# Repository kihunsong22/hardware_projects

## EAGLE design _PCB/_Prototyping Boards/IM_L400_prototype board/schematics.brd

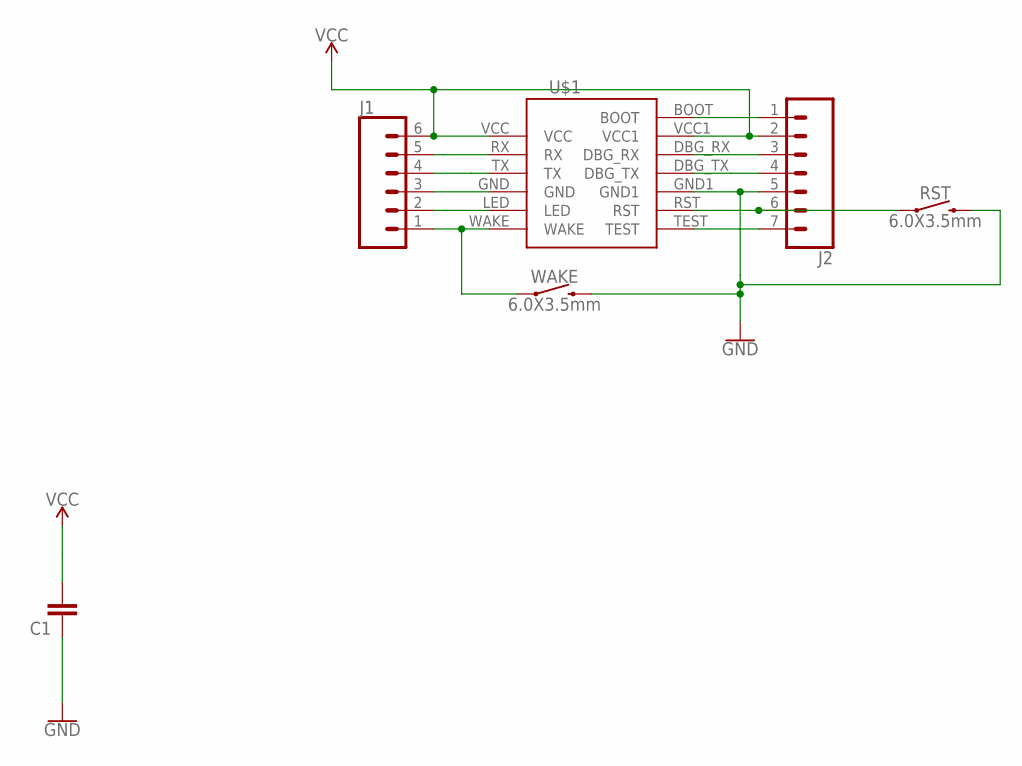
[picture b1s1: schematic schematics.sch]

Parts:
C1: C-EUC0805; C0805
J1: CONN_06LOCK; 1X06_LOCK
J2: CONN_07LOCK; 1X07_LOCK
RST: 6.0X3.5mm; TACTILE_SWITCH_SMD_6.0X3.5MM
U$1: IM-L400
WAKE: 6.0X3.5mm; TACTILE_SWITCH_SMD_6.0X3.5MM

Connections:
GND: C1.1, J1.3, J2.5, RST.2, U$1.GND, U$1.GND1, WAKE.2
unnamed: J1.5, U$1.RX
unnamed: J1.4, U$1.TX
unnamed: J1.2, U$1.LED
unnamed: J1.1, U$1.WAKE, WAKE.1
unnamed: J2.1, U$1.BOOT
unnamed: J2.3, U$1.DBG_RX
unnamed: J2.4, U$1.DBG_TX
unnamed: J2.6, RST.1, U$1.RST
unnamed: J2.7, U$1.TEST
VCC: C1.2, J1.6, J2.2, U$1.VCC, U$1.VCC1

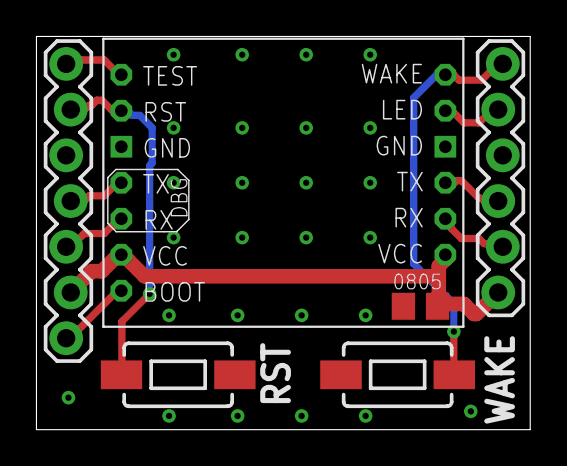
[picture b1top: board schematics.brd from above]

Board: 2 copper layers, 27.4 x 21.8 mm, 6 parts (0 on the bottom side), 11 nets.

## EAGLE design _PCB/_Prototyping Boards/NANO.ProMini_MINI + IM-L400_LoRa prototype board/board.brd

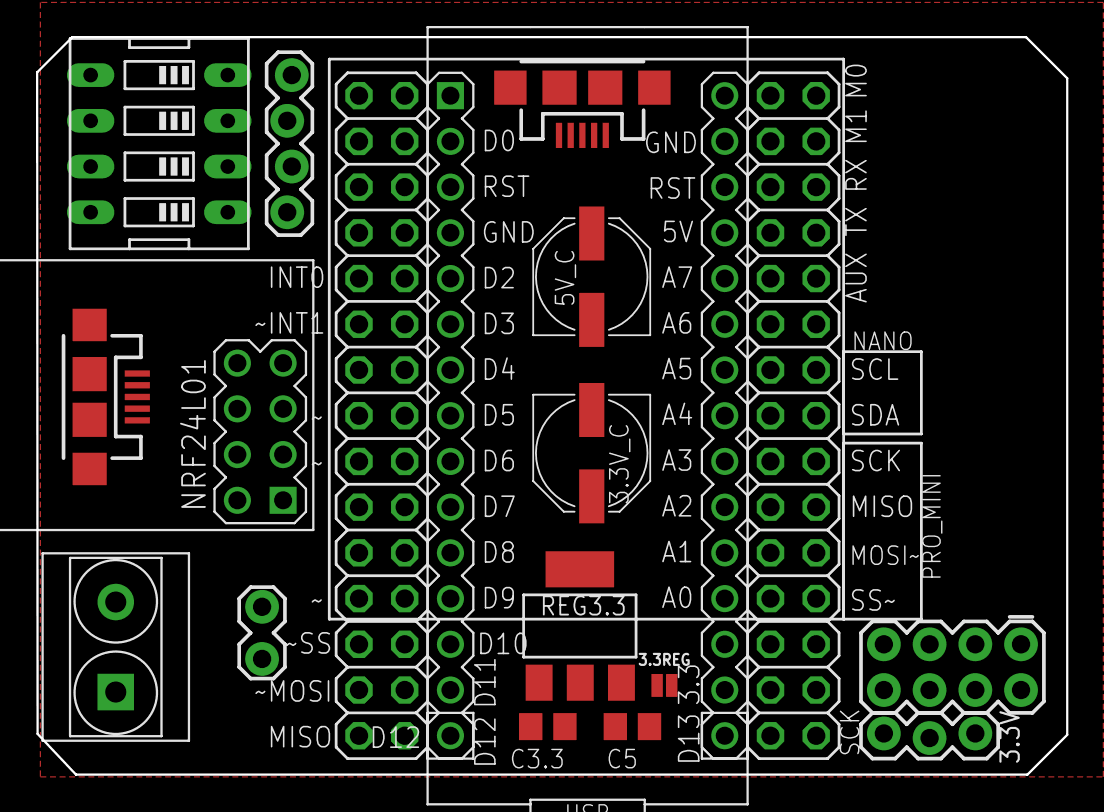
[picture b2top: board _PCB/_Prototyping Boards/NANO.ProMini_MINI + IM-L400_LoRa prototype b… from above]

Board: 2 copper layers, 57.2 x 41.0 mm, 18 parts (0 on the bottom side), 38 nets, no tracks yet.

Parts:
3.3REG: SMT-JUMPER_2_NO_NO-SILK
3.3V: 1X03_LOCK
3.3V_C, 5V_C: PANASONIC_D
5.GND: 2X4
C3.3, C5: 100nF; C0805
J4: 1X04_LOCK
MICRO_1, MICRO_2: USB-MICROB
NANO: ARDUINO-NANO-3.0
NRF24L01: WIRELESS-NRF24L01
PH1, PH2: 2X15
PIN1: 1X02_LOCK
REG3.3: REG1117; SOT223
SW1: EDG-04
T1_5MM: 5mm; H2-5.0-10.5X8.0MM

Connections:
3.3V: 3.3V.1, 3.3V.2, 3.3V.3, 3.3V_C.+, NANO.J2.14, NRF24L01.2, PH1.3, PH1.4
5V: 5.GND.2, 5.GND.4, 5.GND.6, 5.GND.8, 5V_C.+, C5.1, MICRO_1.VBUS, MICRO_2.VBUS, NANO.J2.4, PH1.23, PH1.24, REG3.3.3
A5: NANO.J2.7, PH1.17, PH1.18
A6: NANO.J2.6, PH1.19, PH1.20
A7: NANO.J2.5, PH1.21, PH1.22
CE_NRF: NANO.J1.9, NRF24L01.3, PH2.13, PH2.14
CSN_NRF: NANO.J1.8, NRF24L01.4, PH2.15, PH2.16
GND: 3.3V_C.-, 5.GND.1, 5.GND.3, 5.GND.5, 5.GND.7, 5V_C.-, C3.3.1, C5.2, MICRO_1.GND, MICRO_2.GND, NANO.J2.2, NRF24L01.1, PH1.27, PH1.28, REG3.3.1, SW1.5, SW1.6, SW1.7, SW1.8
MISO_NRF: NANO.J1.4, NRF24L01.7, PH2.23, PH2.24
MOSI_NRF: NANO.J1.5, NRF24L01.6, PH2.21, PH2.22
unnamed: 3.3REG.2, C3.3.2
unnamed: 3.3REG.1, REG3.3.2
unnamed: NANO.J2.13, PH1.5, PH1.6
unnamed: NANO.J2.12, PH1.7, PH1.8
unnamed: NANO.J2.11, PH1.9, PH1.10
unnamed: NANO.J2.10, PH1.11, PH1.12
unnamed: NANO.J2.9, PH1.13, PH1.14
unnamed: NANO.J2.8, PH1.15, PH1.16
unnamed: NANO.J1.15, PH2.1, PH2.2
unnamed: NANO.J1.14, PH2.3, PH2.4
unnamed: NANO.J1.13, PH2.5, PH2.6
unnamed: NANO.J1.12, PH2.7, PH2.8
unnamed: NANO.J1.11, PH2.9, PH2.10
unnamed: NANO.J1.10, PH2.11, PH2.12
unnamed: PIN1.2, T1_5MM.1
unnamed: NANO.J1.7, PH2.17, PH2.18
unnamed: NANO.J1.6, PH2.19, PH2.20
unnamed: PIN1.1, T1_5MM.2
unnamed: NANO.J1.3, PH2.25, PH2.26
unnamed: NANO.J1.2, PH2.27, PH2.28
unnamed: NANO.J1.1, PH2.29, PH2.30
unnamed: J4.1, SW1.4
unnamed: J4.2, SW1.3
unnamed: J4.3, SW1.2
unnamed: J4.4, SW1.1
RST: NANO.J2.3, PH1.25, PH1.26
SCK_NRF: NANO.J2.15, NRF24L01.5, PH1.1, PH1.2
VIN: NANO.J2.1, PH1.29, PH1.30

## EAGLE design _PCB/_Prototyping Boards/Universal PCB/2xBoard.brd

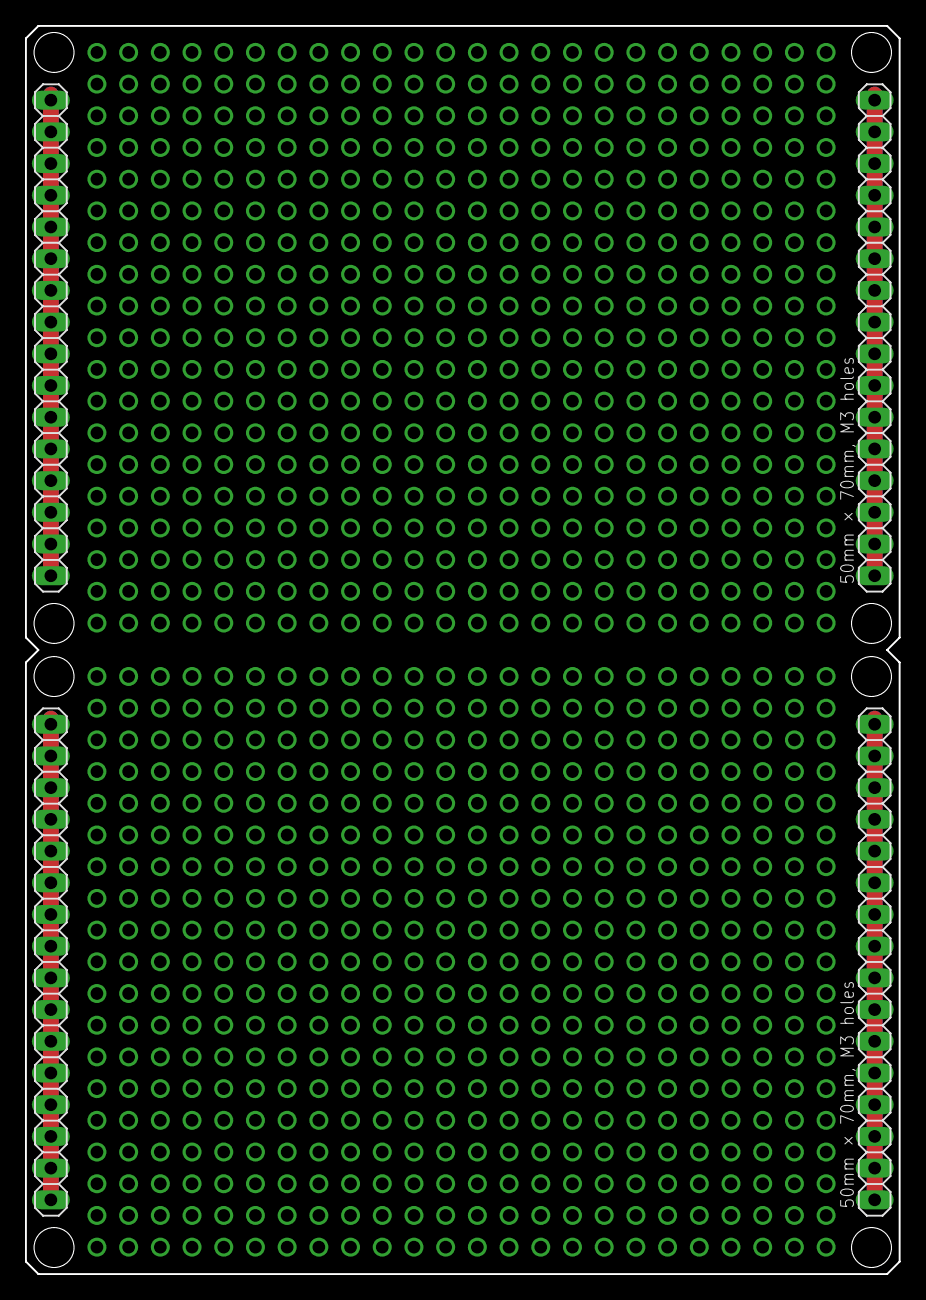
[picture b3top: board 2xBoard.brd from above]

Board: 2 copper layers, 70.0 x 100.0 mm, 4 parts (0 on the bottom side), 4 nets.

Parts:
JP1, JP2, JP3, JP4: 1X16

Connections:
SIDE1: JP4.1, JP4.2, JP4.3, JP4.4, JP4.5, JP4.6, JP4.7, JP4.8, JP4.9, JP4.10, JP4.11, JP4.12, JP4.13, JP4.14, JP4.15, JP4.16
SIDE2: JP3.1, JP3.2, JP3.3, JP3.4, JP3.5, JP3.6, JP3.7, JP3.8, JP3.9, JP3.10, JP3.11, JP3.12, JP3.13, JP3.14, JP3.15, JP3.16
SIDE3: JP2.1, JP2.2, JP2.3, JP2.4, JP2.5, JP2.6, JP2.7, JP2.8, JP2.9, JP2.10, JP2.11, JP2.12, JP2.13, JP2.14, JP2.15, JP2.16
SIDE4: JP1.1, JP1.2, JP1.3, JP1.4, JP1.5, JP1.6, JP1.7, JP1.8, JP1.9, JP1.10, JP1.11, JP1.12, JP1.13, JP1.14, JP1.15, JP1.16

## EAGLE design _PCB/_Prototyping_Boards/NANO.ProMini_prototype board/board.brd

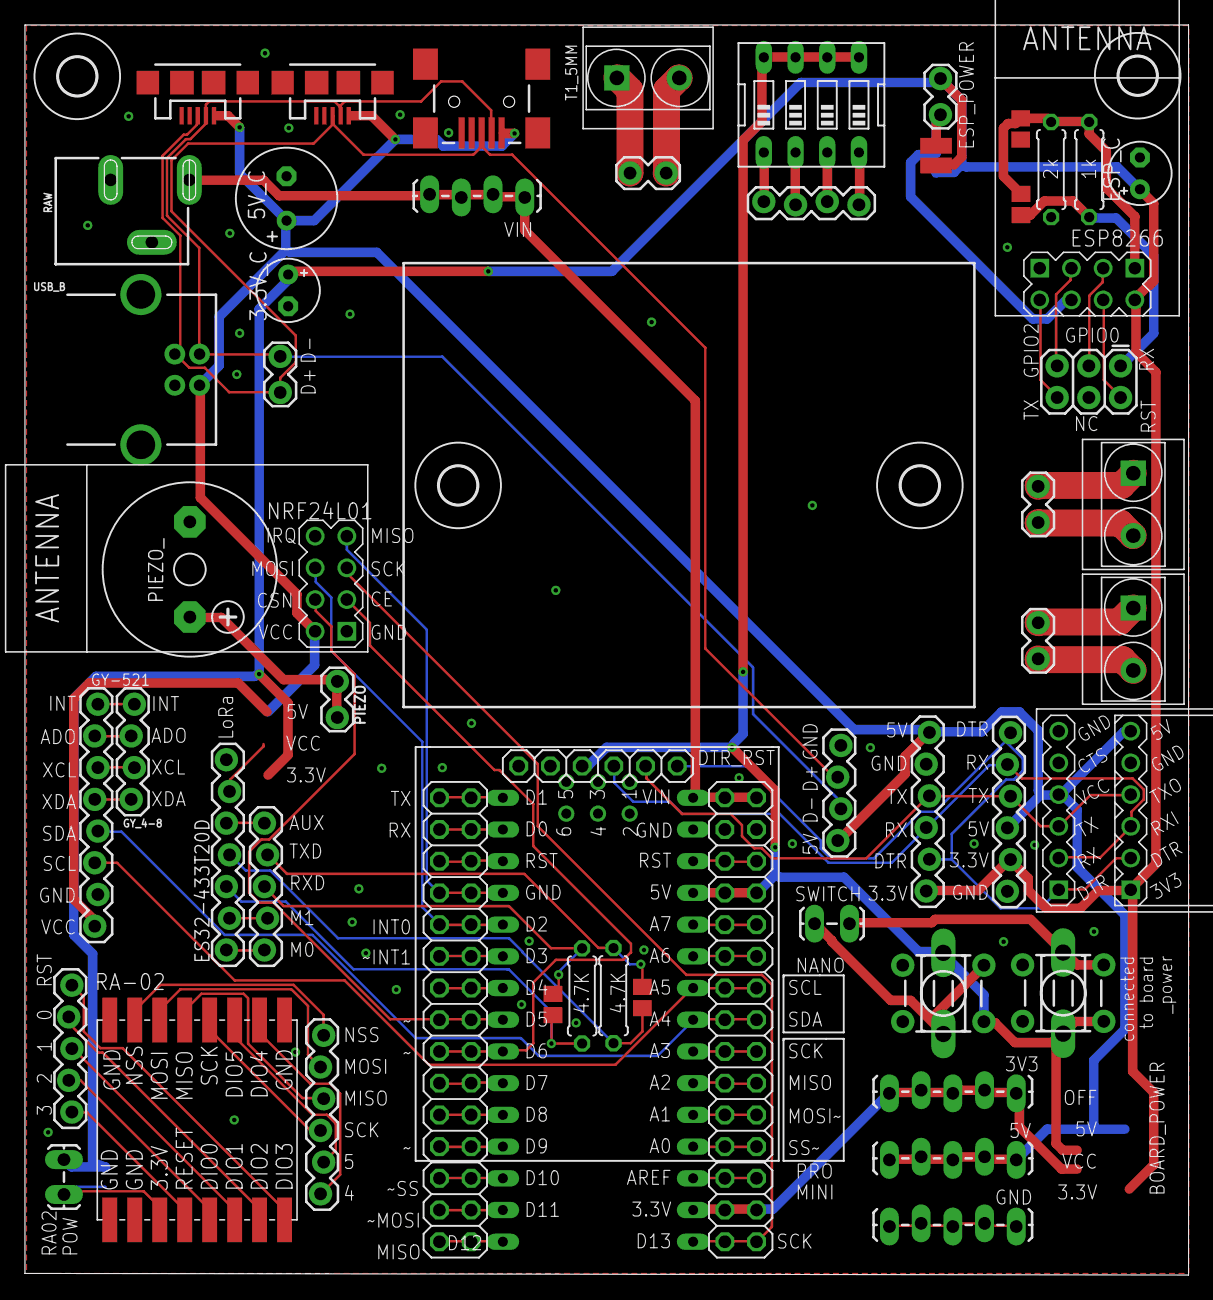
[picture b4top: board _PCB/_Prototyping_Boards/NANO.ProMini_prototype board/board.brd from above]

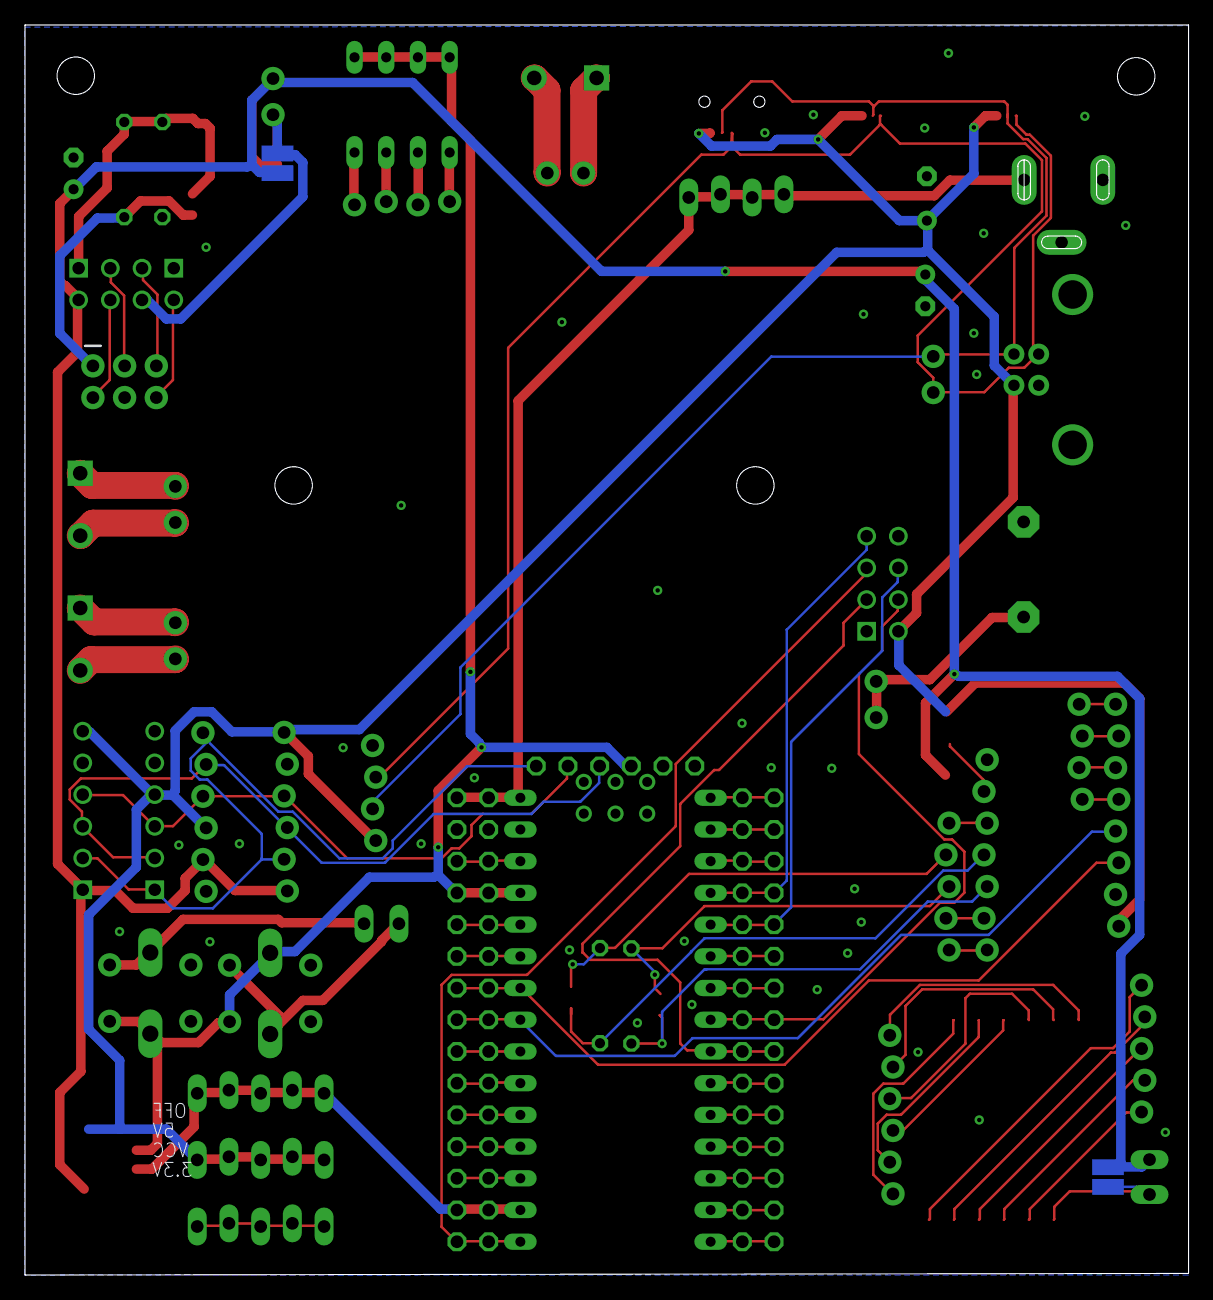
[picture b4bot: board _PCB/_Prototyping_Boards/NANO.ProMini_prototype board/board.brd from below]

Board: 2 copper layers, 93.2 x 100.1 mm, 68 parts (4 on the bottom side), 79 nets.

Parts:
3.3V, 5V: 1X05_LOCK_LONGPADS
3.3V_C: E2,5-5
5V_C: E3,5-8
B1: BREADBOARDMINI; BREADBOARD-MINI
CP2102_USB-SERIAL: USB-SERIAL-CP2102
ES32-433T20D: 1X07_LOCK
ESP1: 1k; 0207/7
ESP1_1, ESP2_1: R2012
ESP2: 2k; 0207/7
ESP8266: WIRELESS-WIFI-ESP-01
ESP_C: E2,5-5
ESP_H: 2X3
ESP_POW: 1X02_LOCK
GND: 1X05_LOCK_LONGPADS
GY-521: 1X08_LOCK
GY_4-8: 1X04_LOCK
H1, H2, H3, H4: MOUNT-HOLE3.0; 3,0
J1, J6: 1X05_LOCK
J2, J3: 1X02_LOCK_LONGPADS
J4, J8: 1X04_LOCK
J5, J7, J9: 1X06_LOCK
MICRO_1, MICRO_2: USB-MICROB
MINI_1: USB_MINI-B_SMT; USB-MINIB
NANO: NANO
NRF24L01: WIRELESS-NRF24L01
PAD1, PAD2, PAD3, PAD4, PAD5, PAD6: SMD1,27-2,54
PH1, PH2: 2X15
PIEZO: 1X02_LOCK
PIEZO_: F/CM12P
PIN1, PIN2, PIN3: 1X02_LOCK
PROMINI_H: 1X06/OCT
R1: 4.7k; 0207/7
R1_1, R2_1: R2012
R2: 4.7K; 0207/7
RA-02: LORA-RA2-SMD
RAW: POWER_JACK_SLOT
S1, S2: MOMENTARY-SWITCH-SPST-PTH-6.0MM; TACTILE_SWITCH_PTH_6.0MM
S3, S4: DTS-3
SW1: EDG-04
T1_5MM, T2_5MM, T3_5MM: 5mm; H2-5.0-10.5X8.0MM
U$1: USB-SERIAL-FT232R
USB_B: USB-B-PTH
USB_DATA: 1X02_LOCK
VIN: 1X04_LOCK_LONGPADS

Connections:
3.3V: 3.3V.1, 3.3V.2, 3.3V.3, 3.3V.4, 3.3V.5, 3.3V_C.+, CP2102_USB-SERIAL.1, ES32-433T20D.6, ESP8266.D2, ESP_C.+, ESP_POW.1, J3.1, J7.2, J9.1, NANO.3.3V, NRF24L01.2, PAD1.1, PAD3.1, PAD5.1, PH1.3, PH1.4
5V: 5V.1, 5V.2, 5V.3, 5V.4, 5V.5, 5V_C.+, CP2102_USB-SERIAL.6, GY-521.1, J7.3, J8.1, J9.6, MICRO_1.VBUS, MICRO_2.VBUS, MINI_1.VBUS, NANO.5V, PH1.23, PH1.24, PROMINI_H.3, U$1.4, USB_B.VBUS
A5: GY-521.3, NANO.A5, PH1.17, PH1.18
A6: NANO.A6, PH1.19, PH1.20
A7: NANO.A7, PH1.21, PH1.22
CE_NRF: NANO.D6, NRF24L01.3, PH2.13, PH2.14
CSN_NRF: NANO.D5, NRF24L01.4, PH2.15, PH2.16
D+_5PIN: J8.3, MICRO_1.D+, MICRO_2.D+, MINI_1.D+, USB_B.D+, USB_DATA.2
D-_5PIN: J8.2, MICRO_1.D-, MICRO_2.D-, MINI_1.D-, USB_B.D-, USB_DATA.1
GND: 3.3V_C.-, 5V_C.-, CP2102_USB-SERIAL.5, ES32-433T20D.7, ESP2.1, ESP2_1.1, ESP8266.A1, ESP_C.-, GY-521.2, J7.1, J8.4, J9.5, MICRO_1.GND, MICRO_2.GND, MINI_1.GND, NANO.GND, NANO.ICSP6, NRF24L01.1, PH1.27, PH1.28, PIEZO_.-, PROMINI_H.1, RA-02.1, RA-02.2, RA-02.9, RA-02.16, RAW.GND@1, S1.1, S2.1, S3.1, S4.2, SW1.5, SW1.6, SW1.7, SW1.8, U$1.6, USB_B.GND
MISO_NRF: NANO.GND1, NRF24L01.7, PH2.23, PH2.24
MOSI_NRF: NANO.D2, NRF24L01.6, PH2.21, PH2.22
unnamed: ES32-433T20D.2, J1.2
unnamed: GY-521.5, GY_4-8.4
unnamed: NANO.AREF, PH1.5, PH1.6
unnamed: NANO.A0, PH1.7, PH1.8
unnamed: NANO.A1, PH1.9, PH1.10
unnamed: NANO.A2, PH1.11, PH1.12
unnamed: NANO.A3, PH1.13, PH1.14
unnamed: GY-521.6, GY_4-8.3
unnamed: GY-521.7, GY_4-8.2
unnamed: GY-521.8, GY_4-8.1
unnamed: ES32-433T20D.1, J1.1
unnamed: J1.4, R1.1, R1_1.1
unnamed: J1.3, R2.1, R2_1.1
unnamed: ES32-433T20D.4, R1.2, R1_1.2
unnamed: NANO.D12, PH2.1, PH2.2
unnamed: NANO.D11, PH2.3, PH2.4
unnamed: NANO.D10, PH2.5, PH2.6
unnamed: NANO.D9, PH2.7, PH2.8
unnamed: NANO.D8, PH2.9, PH2.10
unnamed: NANO.D7, PH2.11, PH2.12
unnamed: ES32-433T20D.5, J1.5
unnamed: PIN1.2, T1_5MM.1
unnamed: NANO.D4, PH2.17, PH2.18
unnamed: NANO.D3, PH2.19, PH2.20
unnamed: PIN1.1, T1_5MM.2
unnamed: PIN2.2, T2_5MM.1
unnamed: NANO.RST1, PH2.25, PH2.26
unnamed: NANO.RX1, PH2.27, PH2.28
unnamed: NANO.TX0, PH2.29, PH2.30
unnamed: PIN2.1, T2_5MM.2
unnamed: PIN3.2, T3_5MM.1
unnamed: PIN3.1, T3_5MM.2
unnamed: PIEZO.1, PIEZO.2, PIEZO_.+
unnamed: GND.1, GND.2, GND.3, GND.4, GND.5
unnamed: J2.1, S1.3, S3.2
unnamed: ES32-433T20D.3, R2.2, R2_1.2
unnamed: J4.1, SW1.4
unnamed: J4.2, SW1.3
unnamed: J4.3, SW1.2
unnamed: J4.4, SW1.1
unnamed: J2.2, S2.3, S4.1
unnamed: J6.1, RA-02.8
unnamed: J6.2, RA-02.7
unnamed: J6.3, RA-02.6
unnamed: J6.4, RA-02.5
unnamed: J6.5, RA-02.4
unnamed: J5.1, RA-02.15
unnamed: J5.2, RA-02.14
unnamed: J5.3, RA-02.13
unnamed: J5.4, RA-02.12
unnamed: J5.5, RA-02.11
unnamed: J5.6, RA-02.10
unnamed: ESP8266.B2, ESP_POW.2, PAD2.1, PAD6.1
unnamed: CP2102_USB-SERIAL.3, J7.5, J9.3, PROMINI_H.4, U$1.2
unnamed: ESP1.1, ESP1_1.1, ESP2.2, ESP2_1.2, ESP8266.D1
unnamed: ESP8266.C2, ESP_H.2
unnamed: ESP8266.C1, ESP_H.3
unnamed: ESP1.2, ESP1_1.2, ESP_H.1
unnamed: CP2102_USB-SERIAL.4, J7.4, J9.4, PROMINI_H.5, U$1.3
unnamed: ESP8266.B1, ESP_H.5
unnamed: ESP8266.A2, ESP_H.6
unnamed: CP2102_USB-SERIAL.2, J7.6, J9.2, PROMINI_H.6, U$1.1
unnamed: J3.2, PAD4.1, RA-02.3
RST: NANO.RST, PH1.25, PH1.26
SCK_NRF: NANO.D13, NRF24L01.5, PH1.1, PH1.2
SDA_GY521: GY-521.4, NANO.A4, PH1.15, PH1.16
VIN: NANO.RAW, PH1.29, PH1.30, RAW.PWR, VIN.1, VIN.2, VIN.3, VIN.4

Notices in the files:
parts and their libraries:
SparkFun-Connectors: Licensing: Creative Commons ShareAlike 4.0 International - https://creativecommons.org/licenses/by-sa/4.0
diy-modules: Released under the Creative Commons Attribution 4.0 International License: http://creativecommons.org/licenses/by/4.0
